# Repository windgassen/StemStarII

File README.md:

# StemStarII
These are the files for the STEMStar II circuit board

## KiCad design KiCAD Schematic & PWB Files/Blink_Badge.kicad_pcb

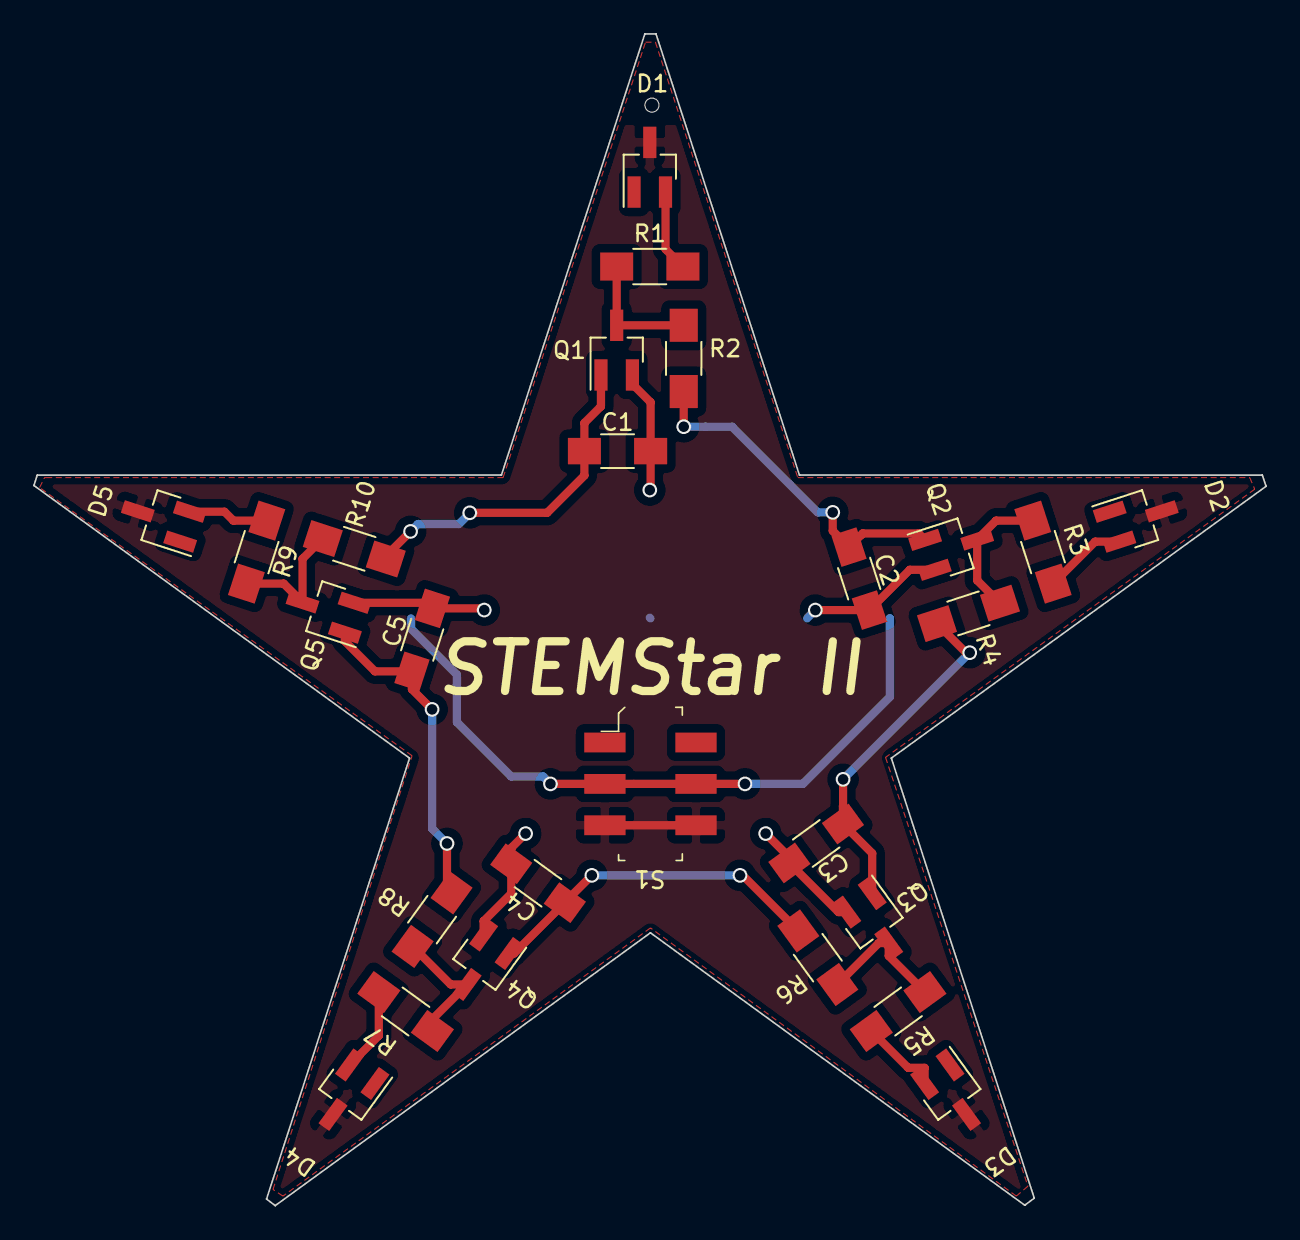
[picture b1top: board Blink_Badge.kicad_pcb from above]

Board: 2 copper layers, 74.4 x 70.8 mm, 28 parts (1 on the bottom side), 18 nets.

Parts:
BT1: BATTERY; Keystone_3024-2_2x20mm-CoinCell
C1, C2, C3, C4, C5: 1uF; C_1206_HandSoldering
D1, D2, D3, D4, D5: LED_Dual_CCA; SOT-23_Handsoldering
MH1: StemStar_Mounting_Pads
Q1, Q2, Q3, Q4, Q5: 2N7002; SOT-23_Handsoldering
R1, R3, R5, R7, R9: 750; R_1206_HandSoldering
R2, R4, R6, R8, R10: 100k; R_1206_HandSoldering
S1: JS202011SCQN; Switch_Slide_JS202011SCQN

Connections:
/+6V: BT1.1, S1.2, S1.5
/+6V_Switched: D1.3, D2.3, D3.3, D4.3, D5.3, S1.3, S1.6
GND: BT1.2, C1.2, C2.2, C3.2, C4.2, C5.2, Q1.2, Q2.2, Q3.2, Q4.2, Q5.2
unnamed: C1.1, Q1.1, R10.1
unnamed: C2.1, Q2.1, R2.1
unnamed: C3.1, Q3.1, R4.1
unnamed: C4.1, Q4.1, R6.1
unnamed: C5.1, Q5.1, R8.1
unnamed: D1.2, R1.1
unnamed: D2.2, R3.1
unnamed: D3.2, R5.1
unnamed: D4.2, R7.1
unnamed: D5.2, R9.1
unnamed: Q1.3, R1.2, R2.2
unnamed: Q2.3, R3.2, R4.2
unnamed: Q3.3, R5.2, R6.2
unnamed: Q4.3, R7.2, R8.2
unnamed: Q5.3, R9.2, R10.2

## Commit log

2023-11-19 Add files via upload
    Revision A STEMStar II Presentation designed to be used with PWB REV A or later.
    -removed slide 2
    -changed images of leds and mosfets to have right and wrong views
    -removed instruction to tin contact pad of battery

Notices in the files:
KiCAD Schematic & PWB Files/Blink_Badge.kicad_pcb:
Creative Commons Licensed
